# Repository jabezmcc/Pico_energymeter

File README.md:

## Raspberry Pi Pico-based True Energy Meter for Appliances

This project couples a simple circuit with a Raspberry Pi Pico to capture the voltage and current waveforms of the power supplying any appliance, allowing a true, cycle-averaged measure of the power consumption.

The circuit uses a step-down transformer and a voltage divider to measure the voltage, and an Amploc current sensor to measure the current.  These signals are amplified and offset to the 0 - 3.3 V input range of the Pico ADCs.  Waveform data is captured over 3 cycles of the 60 Hz AC line supply, and the product of these is integrated.  Phase differences (as would happen with a motor), current spikes (within reason), etc, are automatically captured and integrated, so the measured  power is as correct as possible.

The Pico is programmed using MicroPython.  Voltages on the two ADCs are collected, the power is calculated, and the value is sent to an LCD display.  On a command from a host computer connected via USB, either the power value or a full 3-cycle waveform is transmitted for further processing and display.  The host code is written in Python, with a Qt6-based GUI that displays a chart of the power consumption vs. time, as well as numerical displays of the current power, the average power since starting acquisition, and the total energy consumed. 

#### Circuit description
AC power comes in via a male power receptacle and flows directly to the appliance via a female power socket. One of the wires carrying current passes through an [Amploc AMP25 current sensor](https://amploc.com/products/amp25-open-loop-hall-effect-sensor), which provides a 1.57 V to 3.42 V signal for currents from -25 A to +25 A.  The AC line voltage is also connected to a small step-down transformer producing 13.6 VAC.  I used something salvaged from an old phone system, but any small transformer that gets you down to below 20 V or so will work. 

The voltage from the transformer is further divided down and offset using one of the op amps in a LM358 chip, and fed to ADC0 on the Pico.  The AMP25 output is similarly amplified and offset using the other half of the LM358 to match the ADC range, and fed to ADC1 on the Pico.  5 V power for the Pico, the AMP25, and the LM358 is provided by a small HLK-PM01 supply on board.  

#### Construction notes
Most of the circuit is on a circuit board, detailed in this [KiCAD file](./Pico_energymeter_v2.kicad_pro).

Everything is mounted in a plastic box, with the LCD 1602 display mounted in the lid. The display mount uses a home-made 3D-printed bezel (step file [here](./LCD1602bezel.step)). A short microUSB extender cable is used to bring the Pico's USB connection to a socket on the box wall.

#### Pico code

The MicroPython code that runs on the Pico is contained in the file `powmon_picocode.py`.  This needs to be saved on the Pico as `main.py`.  The code makes use of a LCD1602 I2C Python library (of which there are many) downloaded from [https://github.com/liyuanhe211/Micropython_LCD1602_LCD2004_I2C_Lib](https://github.com/liyuanhe211/Micropython_LCD1602_LCD2004_I2C_Lib).  The file `lib_lcd1602_2004_with_i2c.py` from that site is included here under the name `lyhlcd1602.py`, and must also be stored on the Pico.  The easiest way to put these files on the Pico is by using [Thonny](https://thonny.org/).  

The code does the usual setup for LED, I2C, etc and sets up arrays for voltage and current measurements with 801 points each.  The nominal time between points for 3 cycles of 60 Hz is 3/60/801 =  62.42 $`\mu`$s.  However, there will be inherent small delays so it is necessary to do a measurement to determine empirically how many $`\mu`$s to tell MicroPython to wait between each point in order to ensure exactly 3 cycles with 801 points.  The procedure for this is described below.  

The main while-loop of the code cycles every 0.1 sec.  On each cycle it reads 801 points from the ADCs and calculates the power by multiplying the voltage and the current and integrating via Simpson's rule. The result is multiplied by a calibration factor determined as described below.  

On each cycle the code also reads two bytes from the USB serial port.  These two bytes represent requests from the host code.  If `b'po'` is transmitted this is a request for a power measurement, and the Pico code sends back a string version of the most recent power measurement.  If `b'wa'` is transmitted this is a request for the waveform, and the Pico code does a fresh measurement of the ADCs, packs the data bytes into a structure using `struct.pack()` and transmits these back to the host via `sys.stdout.buffer.write()`.

#### Host code
The host code `energymeter.py` was developed on a Linux system using Python 3.13.3.  I recommend using `pyenv` to set up a virtual environment specifying this version of Python to run it.  The required libraries are listed in `requirements.txt` and can be installed via `pip install requirements.txt`. The code should be fairly easily ported to Windows or MacOS with a few minor adjustments.  Usage should be pretty self explanatory:  click "Take reading" to get a measure of the power, click "Start recording" to begin logging the power, and click "Stop recording" when you want to stop. You will be asked whether you want to save the data.  Click "Show waveform" if you want to see what the voltage and current waveforms look like, and click "Change data destination" if you want to save the data somewhere other than the default location. 

#### Set up and Calibration

1. Timing

In order to make sure we get exactly three cycles of 60 Hz when `ndata` points are acquired, we need to find out how long the Pico takes to measure one data point and then add just enough time to equal `3/60/ndata`. This is done with a separate pair of Pico and host programs.  The program `powmon_picocode_get_base_delay.py` is run on the Pico by loading it into Thonny, pressing run, and then exiting Thonny.  Then the host code `Read_pico_find_dt.py` is run on the host computer.  The host code requests a waveform, the Pico code acquires 801 data points without any extra delay between points, and the voltage waveform is uploaded to the host computer.  An optimizer is then run to fit the waveform to a 60 Hz sine wave with the time interval between points, the amplitude and the phase as free parameters. The time interval resulting from this three-parameter fit is the base delay of the Pico.  This is compared to the time interval necessary to get exactly 3 cycles of 60 Hz, and the difference is reported. Measurements on my system indicate a delay of 12 $`\mu`$s  is required, and that is the value that is hard-coded in the main Pico code `powmon_picocode.py`.  If a value different from 12 $`\mu`$s is observed, the main Pico code should be edited and the definition of the constant `delay_us` changed.     

2. Calibration

Because the ADCs in the Pico measure on a scale of 0 to 65535, it is necessary to do an initial measurement to set the correct scaling factor for the voltage, current and power values.  To do this, a 100 W light bulb is plugged into the box and the actual RMS voltage and current are measured with a multimeter. Voltage is read by touching the hot terminals, and current is measured on the 10 A AC scale with the multimeter in the circuit. Of course ***this must be done with great care*** to avoid getting shocked! The light bulb is assumed to be a fully resistive load, so separate measurements of the voltage and current RMS values can be multiplied to obtain the RMS power.  

Once the RMS voltage and current are known for the 100 W light bulb, the correct scaling factors are determined by running another host program, `calibration.py`, on the host while the normal Pico code `powmon_picocode.py` is running on the Pico.  The RMS voltage and current as determined above are entered, then 'Measure' is pressed.  The power is then measured 20 times at 1 second intervals and the average calculated based on whatever scaling value is hard-coded in `powmon_picocode.py`.  The ratio of the actual RMS power to this measured value is reported as a correction factor that needs to be applied to the scaling factor by editing the definition of the constant `powfact` in  `powmon_picocode.py`.

The voltage and current scale factors are obtained by pressing the 'Measure waveform' button.  Three-cycle waveforms for voltage and current  are retrieved from the Pico and least-squares-fit to a sine wave with amplitude and phase as free parameters.  The scale factors necessary to match the amplitudes to $\sqrt2$ times the RMS values are then reported.  The main code `energymeter.py` should then be edited and the constants `voltfact` and  `curfact` set to these values. Note these values are only used when displaying the waveforms.  The power measurement has a separate scale factor stored in the Pico code.

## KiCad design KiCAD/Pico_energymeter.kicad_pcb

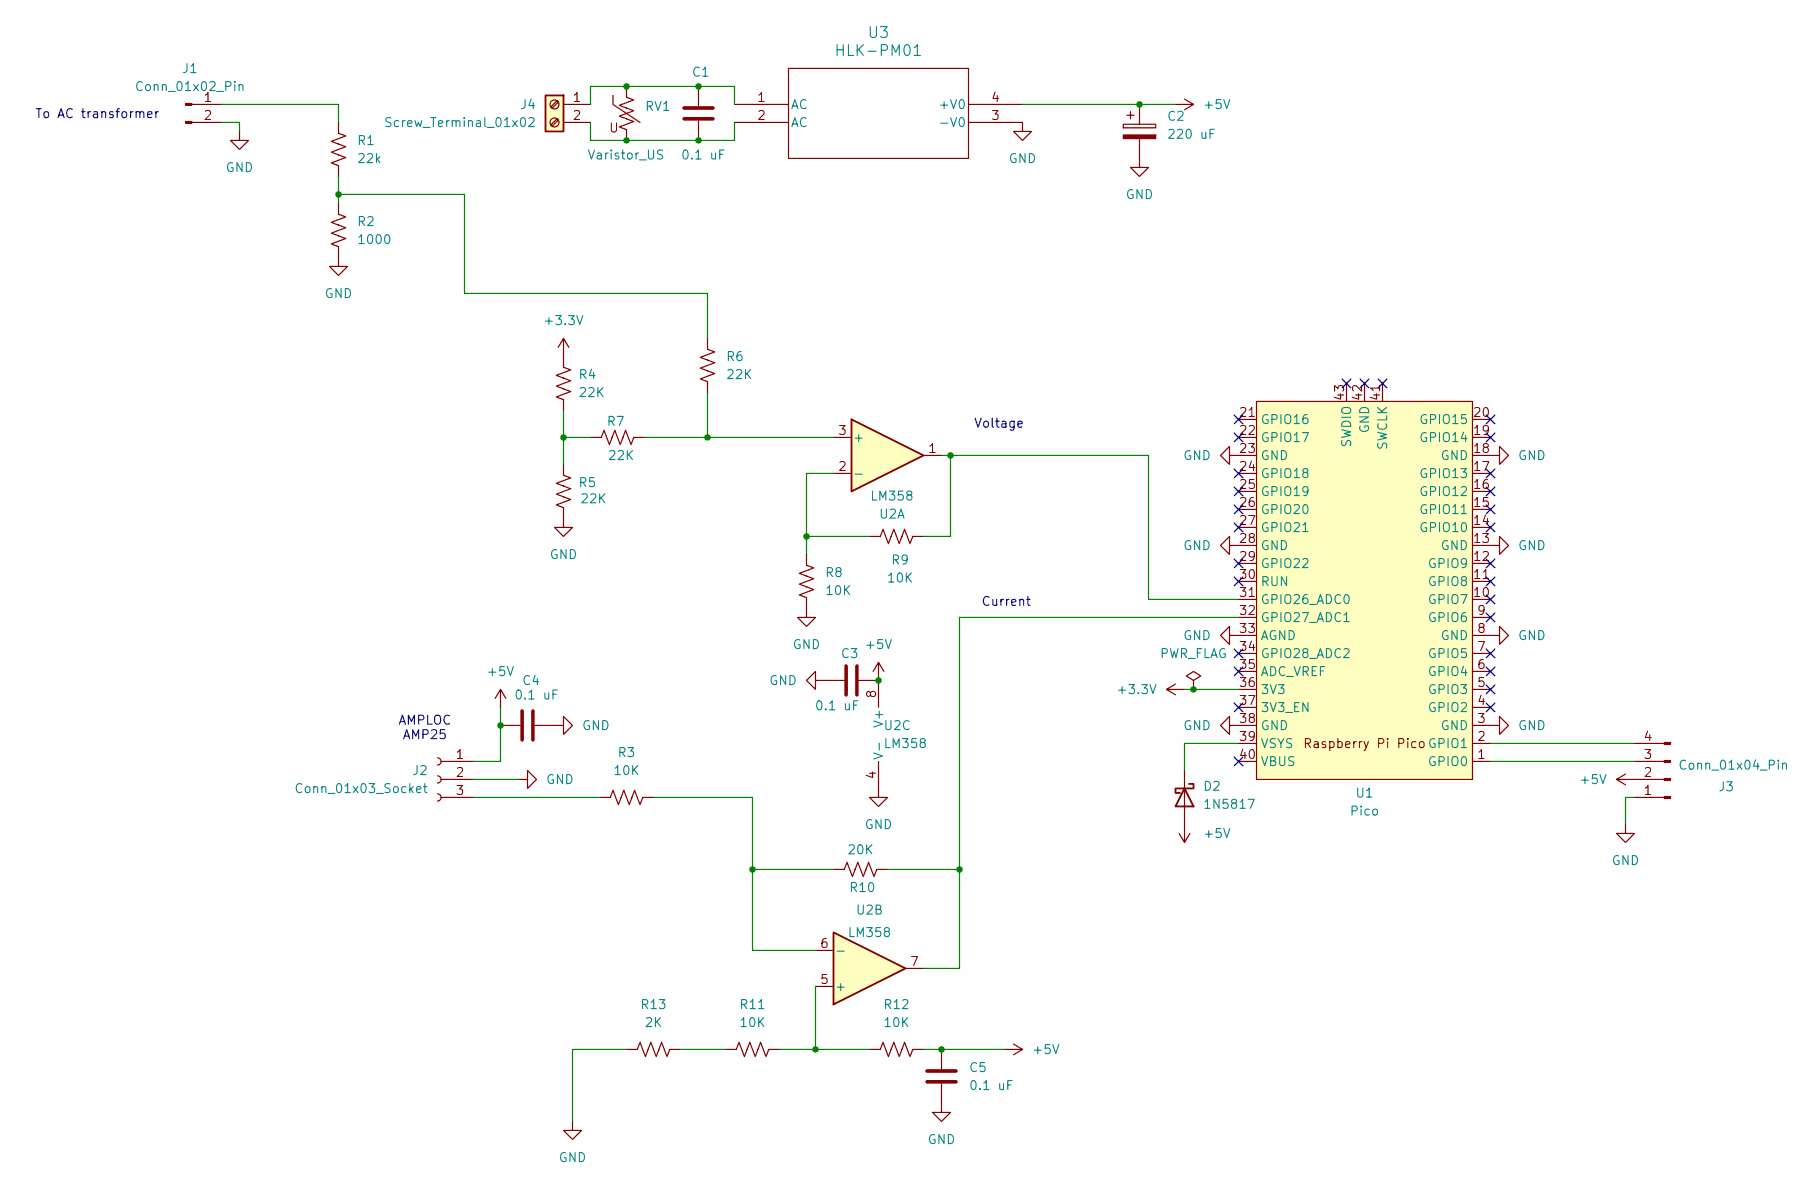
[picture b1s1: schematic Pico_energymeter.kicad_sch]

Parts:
C1, C3, C4, C5: 0.1 uF; C_Rect_L10.3mm_W4.5mm_P7.50mm_MKS4
C2: 220 uF; CP_Radial_D6.3mm_P2.50mm
D2: 1N5817; D_DO-41_SOD81_P10.16mm_Horizontal
J1: Conn_01x02_Pin; PinHeader_1x02_P2.54mm_Vertical
J2: Conn_01x03_Socket; PinSocket_1x03_P2.54mm_Vertical
J3: Conn_01x04_Pin; PinHeader_1x04_P2.54mm_Vertical
J4: Screw_Terminal_01x02; TerminalBlock_bornier-2_P5.08mm
R1: 22k; R_Axial_DIN0207_L6.3mm_D2.5mm_P10.16mm_Horizontal
R2: 1000; R_Axial_DIN0207_L6.3mm_D2.5mm_P10.16mm_Horizontal
R3, R8, R9, R11, R12: 10K; R_Axial_DIN0207_L6.3mm_D2.5mm_P10.16mm_Horizontal
R4, R5, R6, R7: 22K; R_Axial_DIN0207_L6.3mm_D2.5mm_P10.16mm_Horizontal
R10: 20K; R_Axial_DIN0207_L6.3mm_D2.5mm_P10.16mm_Horizontal
R13: 2K; R_Axial_DIN0207_L6.3mm_D2.5mm_P10.16mm_Horizontal
RV1: Varistor_US; RV_Disc_D21.5mm_W4.3mm_P10mm
U1: Pico; RPi_Pico_SMD_TH
U2: LM358; DIP-8_W7.62mm_Socket
U3: HLK-PM01; DIP4_HLK-PM_HLK

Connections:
+3.3V: R4.1, U1.36 (3V3)
+5V: C2.1, C3.2, C4.1, C5.1, D2.2 (A), J2.1, J3.2, R12.2, U2.8 (V+), U3.4 (+V0)
GND: C2.2, C3.1, C4.2, C5.2, J1.2, J2.2, J3.1, R2.2, R5.2, R8.2, R13.1, U1.3 (GND), U1.8 (GND), U1.13 (GND), U1.18 (GND), U1.23 (GND), U1.28 (GND), U1.33 (AGND), U1.38 (GND), U2.4 (V-), U3.3 (-V0)
unnamed: D2.1 (K), U1.39 (VSYS)
unnamed: J1.1, R1.1
unnamed: J2.3, R3.1
unnamed: J3.3, U1.1 (GPIO0)
unnamed: J3.4, U1.2 (GPIO1)
unnamed: C1.1, J4.1, RV1.1, U3.1 (AC)
unnamed: C1.2, J4.2, RV1.2, U3.2 (AC)
unnamed: R1.2, R2.1, R6.2
unnamed: R4.2, R5.1, R7.1
unnamed: R11.1, R13.2
unnamed: R9.2, U1.31 (GPIO26_ADC0), U2.1
unnamed: R10.2, U1.32 (GPIO27_ADC1), U2.7
unnamed: R6.1, R7.2, U2.3 (+)
unnamed: R8.1, R9.1, U2.2 (-)
unnamed: R11.2, R12.1, U2.5 (+)
unnamed: R3.2, R10.1, U2.6 (-)

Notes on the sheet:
Voltage
To AC transformer
Current
AMPLOC AMP25

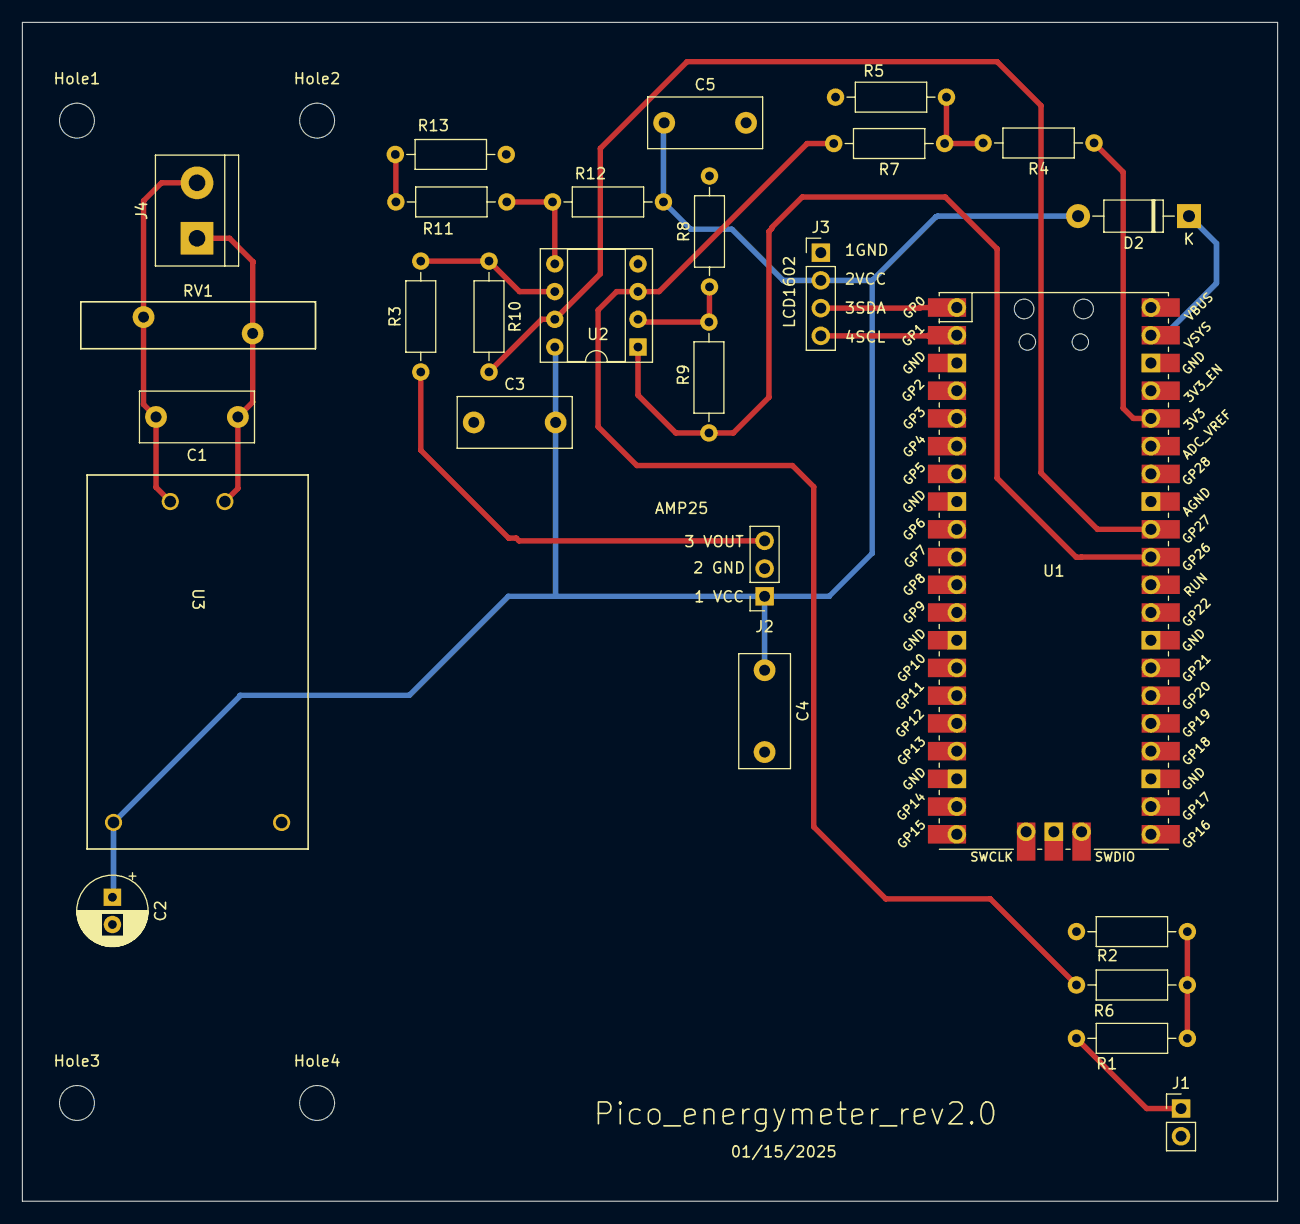
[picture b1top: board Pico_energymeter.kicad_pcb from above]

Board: 2 copper layers, 115.0 x 108.0 mm, 31 parts (0 on the bottom side), 19 nets.

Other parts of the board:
Hole1, Hole2, Hole3, Hole4: MountingHole_3.2mm_M3_ISO7380

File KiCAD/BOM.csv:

"Reference","Value","Datasheet","Footprint","Qty","DNP"
"C1,C3,C4,C5","0.1 uF","~","Capacitor_THT:C_Rect_L10.3mm_W4.5mm_P7.50mm_MKS4","4",""
"C2","220 uF","~","Capacitor_THT:CP_Radial_D6.3mm_P2.50mm","1",""
"D2","1N5817","http://www.vishay.com/docs/88525/1n5817.pdf","Diode_THT:D_DO-41_SOD81_P10.16mm_Horizontal","1",""
"J1","Conn_01x02_Pin","~","Connector_PinHeader_2.54mm:PinHeader_1x02_P2.54mm_Vertical","1",""
"J2","Conn_01x03_Socket","~","Connector_PinSocket_2.54mm:PinSocket_1x03_P2.54mm_Vertical","1",""
"J3","Conn_01x04_Pin","~","Connector_PinHeader_2.54mm:PinHeader_1x04_P2.54mm_Vertical","1",""
"J4","Screw_Terminal_01x02","~","TerminalBlock:TerminalBlock_bornier-2_P5.08mm","1",""
"R1","22k","~","Resistor_THT:R_Axial_DIN0207_L6.3mm_D2.5mm_P10.16mm_Horizontal","1",""
"R2","1000","~","Resistor_THT:R_Axial_DIN0207_L6.3mm_D2.5mm_P10.16mm_Horizontal","1",""
"R3,R8,R9,R11,R12","10K","~","Resistor_THT:R_Axial_DIN0207_L6.3mm_D2.5mm_P10.16mm_Horizontal","5",""
"R4,R5,R6,R7","22K","~","Resistor_THT:R_Axial_DIN0207_L6.3mm_D2.5mm_P10.16mm_Horizontal","4",""
"R10","20K","~","Resistor_THT:R_Axial_DIN0207_L6.3mm_D2.5mm_P10.16mm_Horizontal","1",""
"R13","2K","~","Resistor_THT:R_Axial_DIN0207_L6.3mm_D2.5mm_P10.16mm_Horizontal","1",""
"RV1","Varistor_US","~","Varistor:RV_Disc_D21.5mm_W4.3mm_P10mm","1",""
"U1","Pico","","MCU_RaspberryPi_and_Boards:RPi_Pico_SMD_TH","1",""
"U2","LM358","http://www.ti.com/lit/ds/symlink/lm2904-n.pdf","Package_DIP:DIP-8_W7.62mm_Socket","1",""
"U3","HLK-PM01","HLK-PM01","HLKPM01:DIP4_HLK-PM_HLK","1",""

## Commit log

2025-06-19 commit more files
2025-06-19 fix markdown preview
2025-07-12 Finished Readme.md
2025-07-12 Tweaked Readme.md
2025-07-12 Tweaked Readme.md again
2025-07-12 updated BOM
2025-07-12 tweak ReadMe
2025-07-13 code cleanup
2025-07-19 minor readme.md edits
2025-07-23 slowed readout
2025-07-29 correct schematic
